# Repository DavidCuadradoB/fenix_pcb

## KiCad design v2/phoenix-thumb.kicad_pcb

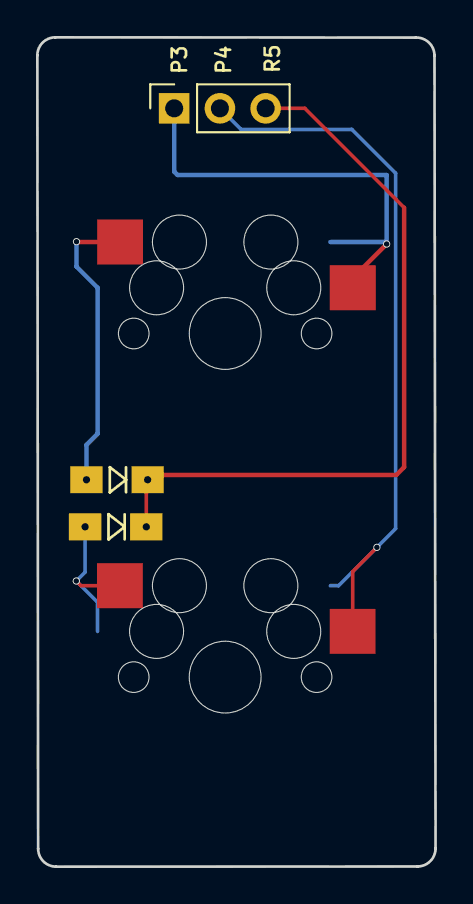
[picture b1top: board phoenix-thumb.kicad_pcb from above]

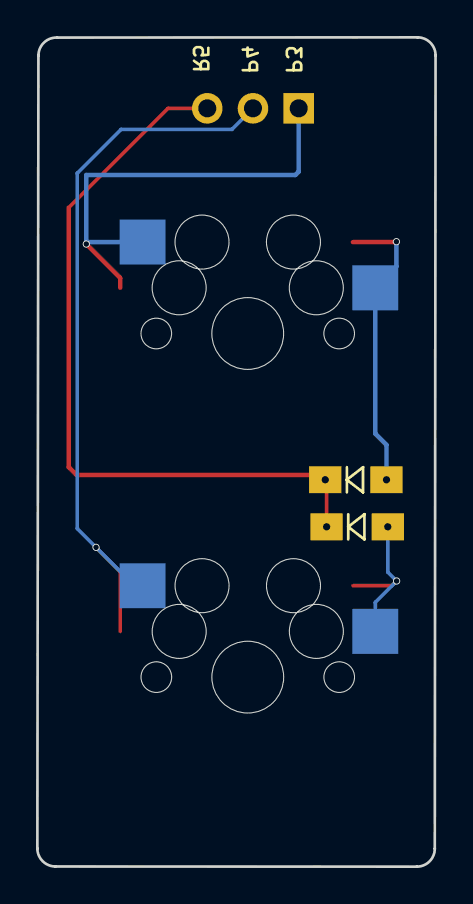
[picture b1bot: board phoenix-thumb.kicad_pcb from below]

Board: 2 copper layers, 22.1 x 46.1 mm, 4 parts (2 on the bottom side), 3 nets.

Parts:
D25, D25#2: D; Diode_SOD123
S2, S7: MX

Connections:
R30: D25#2.1, S2.1
R31: D25.1, S7.1
row5: D25.2, D25#2.2

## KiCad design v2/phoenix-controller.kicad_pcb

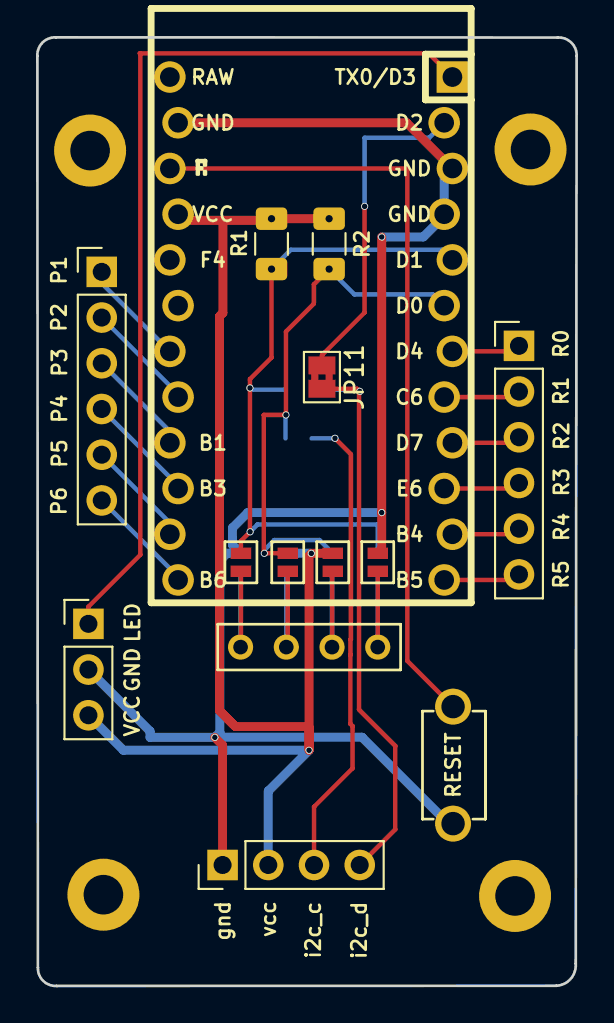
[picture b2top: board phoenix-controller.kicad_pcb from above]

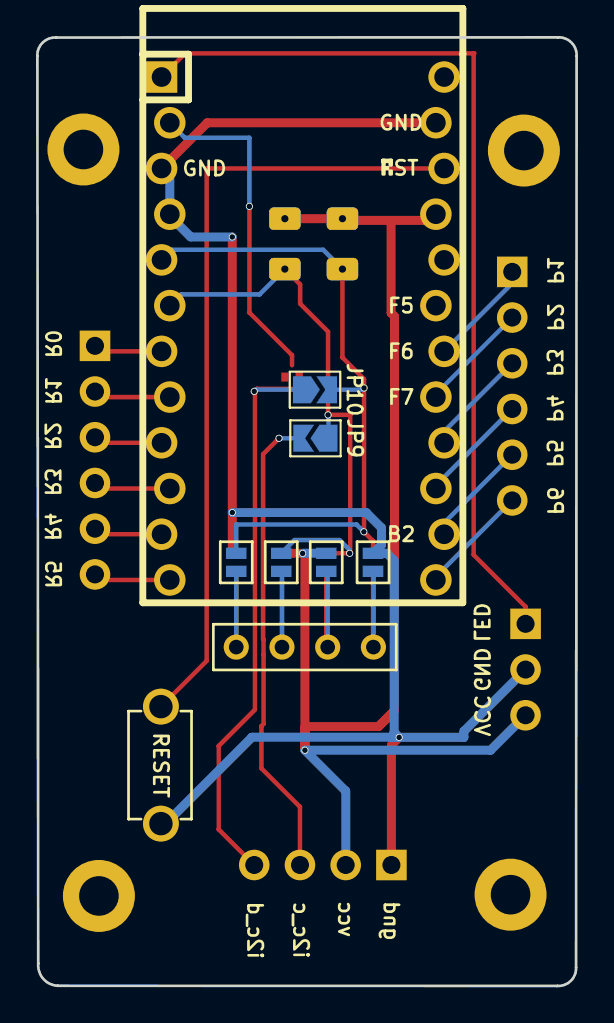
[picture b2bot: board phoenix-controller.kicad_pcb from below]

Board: 2 copper layers, 30.0 x 52.7 mm, 18 parts (11 on the bottom side), 11 nets.

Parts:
J3: OLED; OLED_4Pin
JP1, JP2, JP3, JP4, JP5, JP6, JP7, JP8: Jumper_NO_Small; Jumper
JP9: I2CSCL; SolderJumper-2_P1.3mm_Open_TrianglePad1.0x1.5mm
JP10: IC2SDA; SolderJumper-2_P1.3mm_Open_TrianglePad1.0x1.5mm
JP11: Serial; SolderJumper-2_P1.3mm_Bridged2Bar_Pad1.0x1.5mm
R1, R2: R; R_1206_DoubleSided
RSW1: SW_RST; TACT_SWITCH_TVBP06
TH1, TH2: HOLE; M2_HOLE_PCB
U1: ProMicro; ArduinoProMicro-ZigZag-DoubleSided

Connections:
/i2c_d: JP10.1, JP11.2
GND: JP4.2, JP5.2, RSW1.1, U1.3, U1.4, U1.23
unnamed: J3.1, JP4.1, JP8.1
unnamed: J3.2, JP3.1, JP7.1
unnamed: J3.3, JP2.1, JP6.1
unnamed: J3.4, JP1.1, JP5.1
RESET: RSW1.2, U1.22
SCL: JP2.2, JP7.2, JP9.1, R2.2, U1.6
SDA: JP1.2, JP8.2, JP10.2, R1.2, U1.5
VCC: JP3.2, JP6.2, R1.1, R2.1, U1.21
data: JP11.1, U1.2

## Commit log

2023-04-26 thumb
